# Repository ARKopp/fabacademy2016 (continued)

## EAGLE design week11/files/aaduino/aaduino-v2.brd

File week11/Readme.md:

[BACK to START](../)

[FINAL PROJECT](../final) / [WEEK 1](../week1) / [COMPUTER AIDED DESIGN](../week2) / [COMPUTER-CONTROLLED-CUTTING](../week3) / [ELECTRONICS PRODUCTION](../week4) / [3D SCANNING & PRINTING](../week5) / [ELECTRONICS DESIGN](../week6)  / [COMPUTER-CONTROLLED MACHINING](../week7) / [EMBEDDED PROGRAMING ](../week8) / [MECHANICAL DESIGN](../week9) / [MACHINE DESIGN](../week10) / [INPUT DEVICES](../week11) / [3D MOLDING AND CASTING](../week12) / [OUTPUT DEVICES](../week13) / [COMPOSITES](../week14) / [EMBEDDED NETWORKING & COMMUNICATIONS](../week15) / [INTERFACE AND APPLICATION PROGRAMMING ](../week16) / [APPLICATIONS AND IMPLICATIONS ](../week17) / [INVENTION, INTELLECTUAL PROPERTY, AND BUSINESS MODELS](../week18) / [PROJECT DEVELOPMENT ](../week19)  

# Week 11 - INPUT DEVICES
April 13 - April 20 

[Lecture](http://academy.cba.mit.edu/classes/input_devices/index.html), [Video](http://archive.fabacademy.org/archives/2016/master/videos/04-20/index.html)

~~~
*Weeks Assignment*

* measure something
* add a sensor to a micro controller board that you have designed and read it

~~~

## Hall effect Sensor Board

I was waiting for this assignment as I already wanted to measure the speed of my penny board for some time so I decided to make the Hall effect Sensor Board.

First I looked in the Fab Academy Inventory for the parts number of the Hall Sensor called A1301 from Allegro with the Part Number 620-1021-1-ND and then I looked on the Digikey website for the [datasheet](http://www.digikey.de/product-search/de?keywords=620-1021-1-ND). If you would order it from Digikey Germany a sensor would be 1,77€ when you buy ten the cost would be 1,38€.

### The Hall Effect (part 2 on the [Output](../week13) page)

The Hall Effect describes a voltage difference across an conductor whenever a magnetic field is applied in a direction prependicular to the flow of the current of the conductor.

This means whenever the hall sensor detects a magnet it outputs a High Voltage to its Output pin (VOUT). So by clueing a magnet to the wheel of my pennyboard and putting the Hall Sensor Board next to it I can measure the times I get an Output and then with the radius of my wheel I can calcualte the speed of my board in m/s and km/h.

After reading the datasheet I understood that the Hall Sensor A1301 I got has a maximum Output voltage of 50% of the input Voltage and the Output Voltage proportional to the magnetic field supplied. So I decided to use a neodyne magnet to make sure I get a good output. 

### Bill of Materials

SMD Components for the Hall Sensor:	

* IC2 A1324 (SOT-23) (Hall Sensor)
* FTDI Connector
* 2x3 ISP Connector
* Attiny45
* 10k Resistor
* 1uF Capacitor
* neodyn magnet
* a skaeteboard

I also decided to add 2 LEDs.

* 2 X LED green
* 2 X Resistor 499 Ohm 

Neils design I started with.

### My Schematic

I got all the components together and added them to my schematic. I just  could not find the hall sensor at first in eagle.  Finally I looked in the datasheet and found that the name for the hall sensor is A1324-26 or SOT-23. With SOT-23 I found it at last. I  decided this time to also connect all the components to understand the schematic better. The LEDS I connected to MISO and to MOSI. Also I added GND and VCC to all the components. I had to look in another library for them called Supply1.

### Setting up your libraries correctly

After that problem of not finding the components I did some more research into how I can set up my libraries correctly. I figured out that I have to click on the button "load all libraries". I also installed the adafruit library. [This tutorial](https://learn.sparkfun.com/tutorials/how-to-install-and-setup-eagle/using-the-sparkfun-libraries) on sparkfun helped me out. 
And now I finally see all the libraries wenn I click on add components. 

### Designing the traces

To make things a bit more fun I wanted to make a space invader design of my board. So I first drew a rough design with the eyes on top but I did not manage to connect all the components without using 0Ohm Resistors so I took Neils Design as a guideline and went from there. I also put the leds in the bottom. Then I did a first export and overlaid it with a space invader in gimp. I realized I need much more practice in gimp. I could not use photoshop because I do not have a license anymore. 

After like 15 iteration going back and forth between eagle and gimp making the traces smaller and splitting up the pads I finally got my final space invader hall sensor board Version1 at the end of the day.

To get the design through the Design Rules I had to make the traces smaller. Still I did not manage to go through the hall sensor with the ground but I will fix that later with my knife.  

###  Prepare and Mill

My first try was a fail as I used 8mil in eagle Design Rules instead if 16 mil so the traces where to small. 

So I changed the Design Rules to 16 mil and exported the boad again and did the gimp operation.

### Postprocess, Stuffing and Soldering

***Update 23. April***

Finally in Valldaura on Saturday I finished stuffing and soldering the Invader. 

Before soldering I used my knife to get rid of some thin copper in between the traces. 

I think I got these problems because I made my traces thinner and then I would need to put in fabmodules that I want more the 50% overlap. 

### Connecting the Cables

This time we are using Rx, 5v and GND of the FTDI cable and connect them to the Invader.  

### Flash Attiny with Neils C code

For programing I saved the make, the c and the python file from the academy site in one directory and opened the folder in Terminal.

```
sudo make -f hello.mag.45.make program-usbtiny
```

and it worked. 

### Program Attiny with Neils Python Code

Then I tried to run the python program.

I needed to install brew, python and pyserial

```
brew install python
```

```
python hello.mag.45.py /dev/tty.
```

And then hit TAB to autocomplete your serial port. In my case it was this. 

```
python hello.mag.45.py /dev/tty.SLAB_USBtoUART
```

But I got an error that the serial modul is not installed. So I installed it. 

```
sudo easy_install pyserial
```

Now I am getting an error that the port is not working.

After not getting it to work with my FTDI Cable I used a different Cable and got it to worked. 

***Update 30. April 2016:***

It was not the cable I have just connected the pins wrongly. 

```
python hello.mag.45.py /dev/tty.usbserial
```

Also when I put a magnet close to it it worked. 

To show the output of the sensor I installed [python-tk](https://wiki.python.org/moin/TkInter) before  which is a python Web User Interface.

### Change the code to turn on the LEDs

Ok the next step is to look into the C ode Neil and change it to turn on my LED. I looked at the C Code but I still understand too little C so I decided to switch to the Arduino IDE. 

First I looked at the [Attiny45 Datasheet ](http://www.atmel.com/images/atmel-2586-avr-8-bit-microcontroller-attiny25-attiny45-attiny85_datasheet-summary.pdf) to find out the pin Numbering and then also googled what would be the pins then in Arduino.  

I remember I connected the LEDs to MISO and MOSI which would be Leg6/Pin 1 and Leg5/PIN0.

I opened the Ardunio IDE, chose Platine --> ATtiny x5 series, Chip --> Attin45, Clock --> 8Mhz internal (standard is 1mhZ), Port --> dev/cu.SLAB_USBtoUART and --> Programmer USBtinyISP. 

The upload workded but I do not get the LEDs to turn on. I tried every pin. I think that is a great strategy to find the the right pin. 

So first I checked the the LEDs again. I have soldered them correctly with the Green Line to the Ground. So I check the Value again. I used red Led and after looking into the [Fabacademy Inventory](https://docs.google.com/spreadsheets/d/1U-jcBWOJEjBT5A0N84IUubtcHKMEMtndQPLCkZCkVsU/pub?single=true&gid=0&output=html) I found the Red Led had the number 160-1167-2-ND. Looking that up on the digikey website I found the Forward Voltage is 1.8 V and the forward current is 40 mA which resulted in a Resistor of 82 Ohms and I am using 499 Ohms at the moment so I will change the resistor to 100 Ohms. 

In [Output Devices](../week13) I resolved that issue finally and got the LEDs to light up. 

## Otherduino

I already tried to cut the Otherduino as a second project with my new othermill but I used only a once sided FR2 board and the design was two sided. I only used the mill for two cuts but the otherplan software is great. You can directly use the brd files from Eagle and do not have to prepare traces and outline images in gimp or photoshop.

I will try again when I am home in Munich. There is a great [instructable](http://www.instructables.com/id/Unlimited-Arduino-clones-the-Otherduino/?ALLSTEPS) for it. 

**Update 3. Mai 2015:**

Now I got a 2 sided FR2 and I tried to cut the Arduino again. It cut beatfifully with the Othermill I just had to postprocess a little. The machine is great it tells you when to change tool and you can easily produce two sided PCBs

**The process with the Othermill:** 

Bill of Material (all through hole components)

* Circuit board, double-sided
* Clock crystal, 16MHz
* Resistor, 10K*
* 2x Capacitor, 0.1uF
* 2x Capacitors, 22pf
* LED, amber and green or pick your two favorite colors*
* Resistors, 220 ohm (2)*
* Male header, 6-pin, right angle
* Female headers, 20-pin, straight (2)
* ATmega328 microcontroller with Arduino bootloader 
* Chip socket, 28-pin

I did not buy any of the components but looked around at my used electronics and found all the parts. 

First I soldered the Vias which are the connections between the bottom and the top. 

The Otherduino next to my first [Arduino Duemilanove from 2009](https://www.arduino.cc/en/Main/arduinoBoardDuemilanove) which I took the ATmega328 chip and the 16 mhz clock from. 

Then I soldered the chip and the other components. At first I soldered the chip wrongly so I had to desolder it and resolder it.

I checked everything put I could not upload a sketch yet. 

***Update 23. Mail 2016***

I checked all connections and was able to upload a sketch but could not get the light to blink.

I will try to get anothter light to blink tomorrow.

Optional external power materials:

* DC barrel jack, 2.1mm if you want to connect to a wall-wart style power supply
* Regulator, 5V if you want to regulate the wall jack or other power supply to 5V; some are already 5V
* Regulator, 3.3V if you want the option of 3.3 volts. If you want a barrel jack, the 5V regulator is also required.
* Capacitor, 10uF* for each regulator; you'll need two if you're using both regulators

## AAduino

In this week I saw an article on techcrunch of an Arduino in a AA Battery case.

I am also getting together all the components to make [this arduino](https://github.com/kanflo/aaduino) as well. 

* 1/100 flat and mill (
* [x] double sided PCB
* [x] ATMega328p --> [digikey](http://www.digikey.com/product-detail/en/atmel/ATMEGA328P-AUR/ATMEGA328P-AURTR-ND/2357086))
* [ ] temp sensor DS18B20 -> [digikey](http://www.digikey.com/product-detail/en/maxim-integrated/DS18B20/DS18B20-ND/420071)
* [x] 1 x 0603 10K resistor
* [ ] 5 x 0603 0.1uF ceramic capacitors
* [ ] 1 x 0603 1uF ceramic capacitor
* [x] 0603 10uF ceramic capacitor
* [ ] SMT ceramic resonator 16.0MHz
* [x] 2x3 Header
* [x] 3x1 Header
* [ ]  RFM69C Sub-GHz transceiver module

***Update 19. Mai 2016:***

After doing almost all output device boards I got a better understanding of Eagle. I think taking a design of somebody else and look for the components and then change it is a great way to get even a step further. 

[Here](https://nathan.chantrell.net/20130923/tiny328-mini-wireless-arduino-clone/) are all the files and a good explanation. 

## Other Input Devices I want to do later

### Switch

* Attiny45
* Switch
* 2x3 Connector
* FTDI Connector
* 10k 
* 1uF

### Motion

* Attiny45
* FTDI
* 2x3 ISP
* 10k
* 1uF
* HC-Sr04

### Distance

* HC-SR501
* Attiny45
* 1uF
* 10k
* FTDI
* 2x3 ISP

### Temperature

* 4x10k
* 1uF
* FTDI
* Attiny45

### Light

* 49.9k
* Attiny45
* 10k
* T1
* 1uF

### Acceleration 

* ADXL343
* 3 x 10K
* 3V Regulator
* 2x3 ISP Connector
* 1uF
* FTDI

### Sound

* FTDI 
* Attiny45
* 2x3 ISP
* 4 x 10k
* O Ohm
* 3x  1 uF

### Step Response

#

* 2x2 ISP
* 2x3 ISP
* Attiny 45
* 10K
* 1uF
* 1M
* FTDI

## Project Files

[Download](https://drive.google.com/folderview?id=0B3iYmii-HJ7TaWk0RDZWTGktM00&usp=sharing) all project files from this assignment from my Google Drive or directly from here. 

[hall_sensor.brd](./files/hall_sensor/hall_sensor.brd)

[hall_sensor.sch](./files/hall_sensor/hall_sensor.sch)

[hall_sensor_outline.png](./files/hall_sensor/hall_sensor_outline.png)

[hall_sensor_traces.png](./files/hall_sensor/hall_sensor_traces.png)

[hello.mag.45.make](./files/hall_sensor/hello.mag.45.make)

[hello.mag.45.c](./files/hall_sensor/hello.mag.45.c)

[hello.mag.45.py](./files/hall_sensor/hello.mag.45.py)

[blink_input.ino](./files/blink_input/blink_input.ino)

[Otherduino.brd](./files/otherduino/Otherduino5r.brd)

## Learnings

 * Deeper knowledge in Gimp now
 * Code in C
 * Calculate LED Resistors
 * Solder Vias
 * Mill a two sided board
 * Troubleshot a PCBr

## Feedback

[Twitter](http://www.twitter.com/andreaskopp) me or [email me at andreasrkopp at gmail dot com](mailto:andreasrkopp@gmail.com).

[BACK to TOP](../week11)

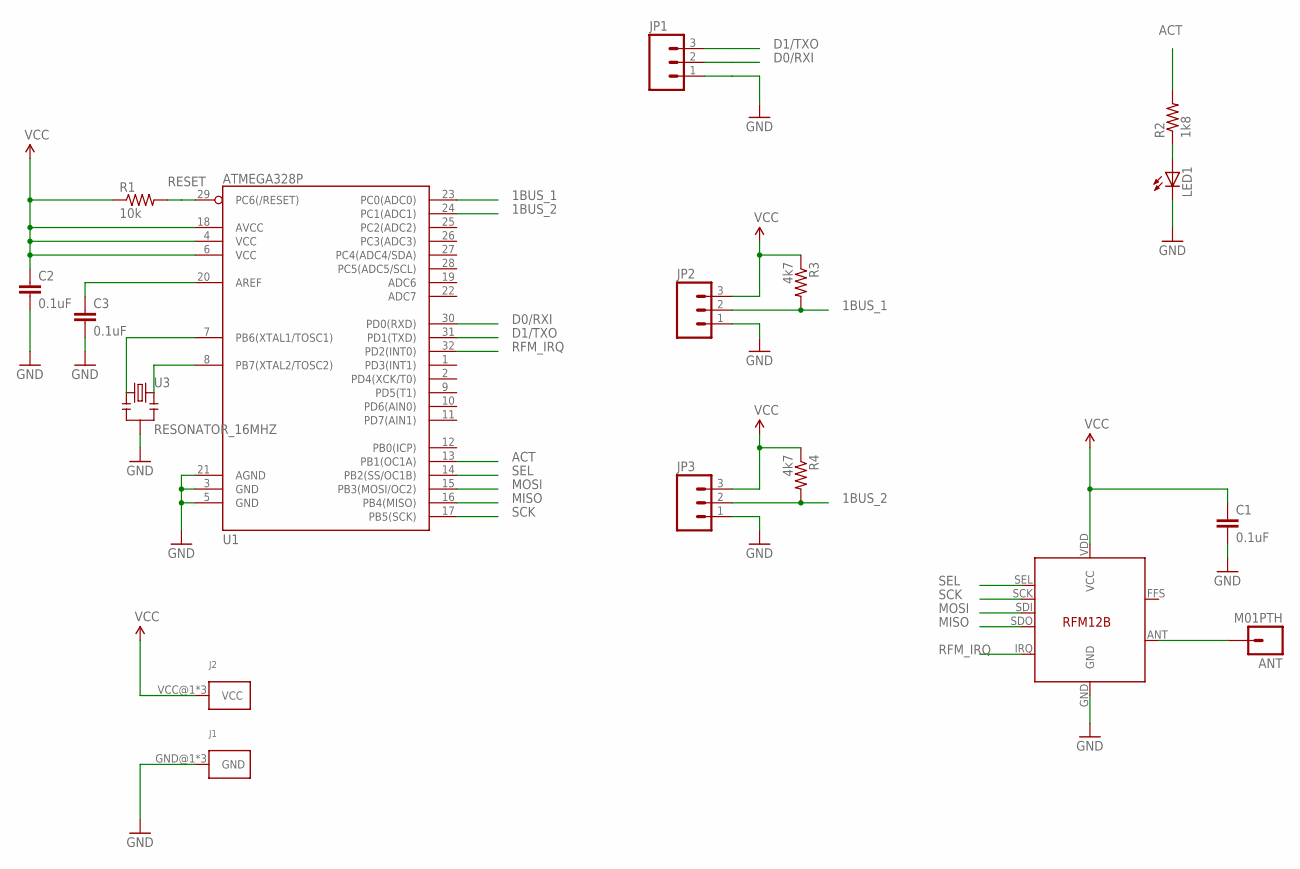
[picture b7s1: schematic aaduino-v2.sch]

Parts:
ANT: M01PTH; 1X01
C1, C2, C3: 0.1uF; 0603-CAP
J1: KEYSTONE-629; KEYSTONE_AA_AAA_BATTERY_TERMINAL-629
J2: KEYSTONE-637; KEYSTONE_AA_AAA_BATTERY_TERMINAL-637
JP1, JP2, JP3: M03PTH; 1X03
LED1: LED0603; LED-0603
R1: 10k; 0603-RES
R2: 1k8; 0603-RES
R3, R4: 4k7; 0603-RES
U1: ATMEGA328P; TQFP32-08
U2: RFM12B
U3: RESONATOR_16MHZ; RESONATOR_SMD

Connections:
1BUS_1: JP2.2, R3.2, U1.23 (PC0(ADC0))
1BUS_2: JP3.2, R4.2, U1.24 (PC1(ADC1))
ACT: R2.2, U1.13 (PB1(OC1A))
D0/RXI: JP1.2, U1.30 (PD0(RXD))
D1/TXO: JP1.3, U1.31 (PD1(TXD))
GND: C1.2, C2.2, C3.2, J1.GND@1, J1.GND@2, J1.GND@3, JP1.1, JP2.1, JP3.1, LED1.C, U1.3 (GND), U1.5 (GND), U1.21 (AGND), U2.GND, U3.2
MISO: U1.16 (PB4(MISO)), U2.SDO
MOSI: U1.15 (PB3(MOSI/OC2)), U2.SDI
unnamed: LED1.A, R2.1
unnamed: C3.1, U1.20 (AREF)
unnamed: U1.7 (PB6(XTAL1/TOSC1)), U3.1
unnamed: U1.8 (PB7(XTAL2/TOSC2)), U3.3
unnamed: ANT.1, U2.ANT
RESET: R1.2, U1.29 (PC6(/RESET))
RFM_IRQ: U1.32 (PD2(INT0)), U2.IRQ
SCK: U1.17 (PB5(SCK)), U2.SCK
SEL: U1.14 (PB2(SS/OC1B)), U2.SEL
VCC: C1.1, C2.1, J2.VCC@1, J2.VCC@2, J2.VCC@3, JP2.3, JP3.3, R1.1, R3.1, R4.1, U1.4 (VCC), U1.6 (VCC), U1.18 (AVCC), U2.VDD (VCC)

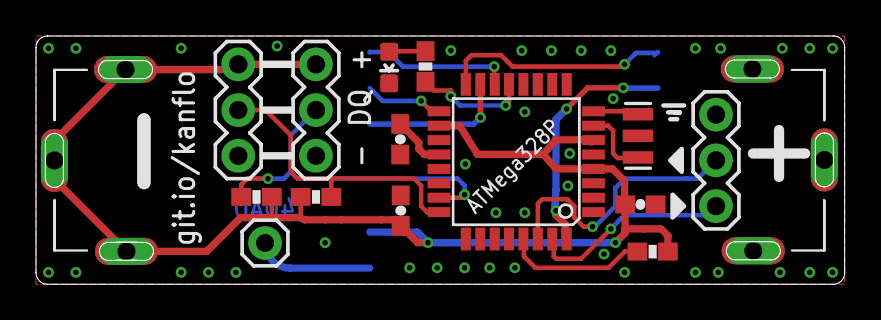
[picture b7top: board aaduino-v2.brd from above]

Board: 2 copper layers, 44.9 x 13.8 mm, 17 parts (1 on the bottom side), 18 nets.

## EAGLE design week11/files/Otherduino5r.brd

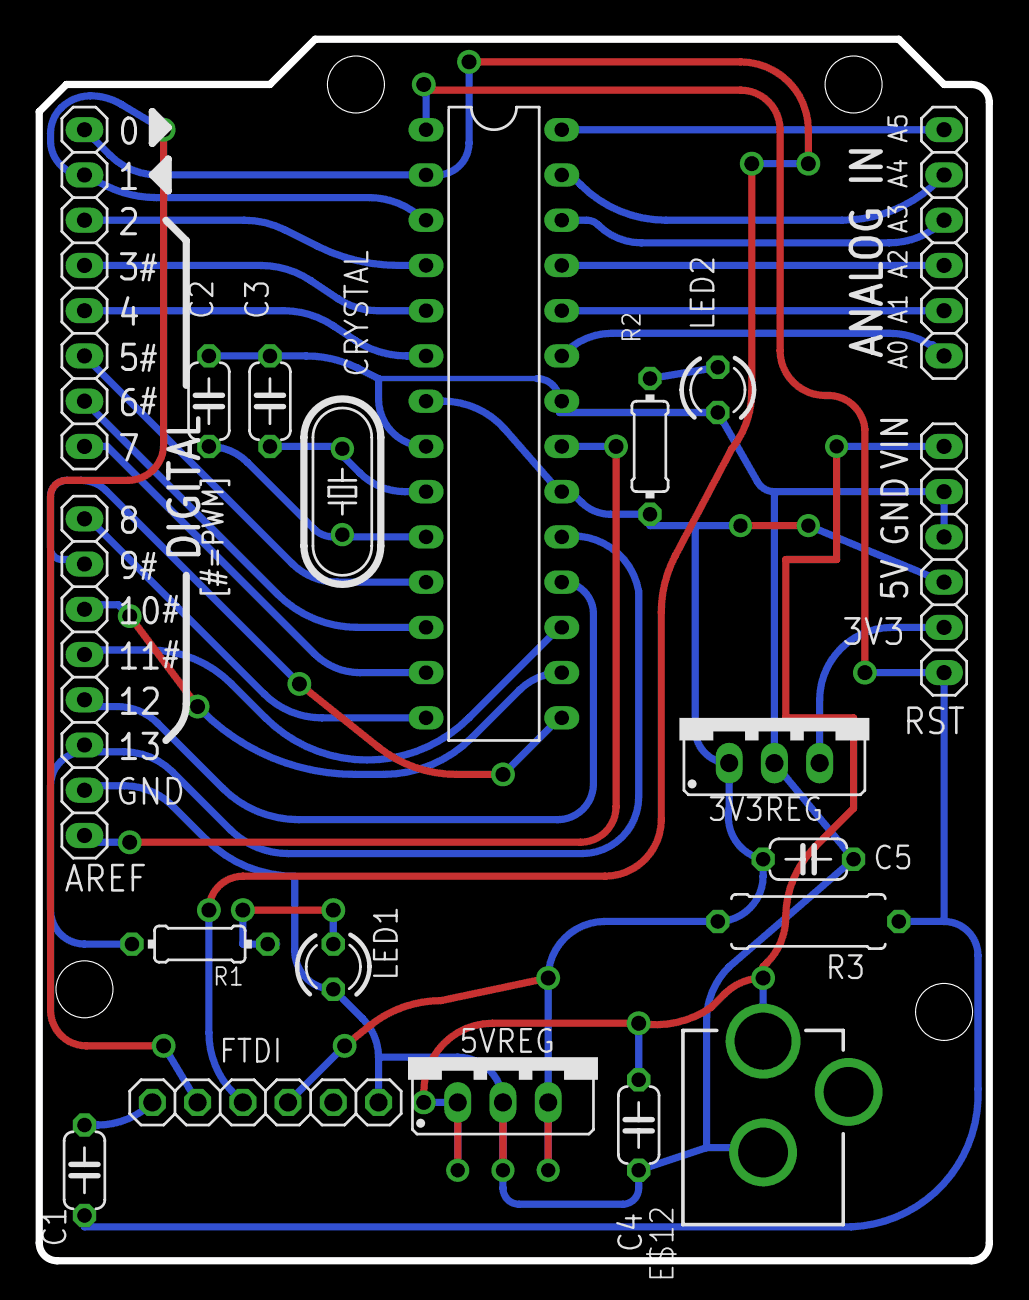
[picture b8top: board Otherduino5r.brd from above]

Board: 2 copper layers, 53.3 x 68.6 mm, 20 parts (0 on the bottom side), 31 nets.

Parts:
3V3REG, 5VREG: 78XXS
AD, AD1: 6x1F-H8.5; 1X06
C1: 0.1uF; C050-024X044
C2, C3: 22pF; C050-024X044
C4, C5: 10uF; C050-024X044
CRYSTAL: 16MHz; HC49/S
E$12: DCJACK_2MM_PTH
FTDI: 1X06
IOL, IOL1: 8x1F-H8.5; 1X08
LED1, LED2: LED3MM
R1, R2: 220; 0204/7
R3: 10k; 0309/10
ZU4: ATMEGA328P-PU; DIL28-3

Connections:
S$1: LED1.A, R1.1
S$2: IOL.3, ZU4.4
S$4: FTDI.5, IOL.2, ZU4.3
S$5: IOL.4, ZU4.5
S$6: IOL.5, ZU4.6
S$9: C3.1, CRYSTAL.1, ZU4.9
S$10: 3V3REG.OUT, AD1.2
S$11: 5VREG.IN, AD1.6, C4.1, E$12.PWR
S$14: C2.1, CRYSTAL.2, ZU4.10
S$16: IOL.7, ZU4.12
S$17: IOL.8, ZU4.13
S$18: IOL1.1, ZU4.14
S$19: IOL1.2, ZU4.15
S$20: IOL1.3, ZU4.16
S$21: IOL1.4, ZU4.17
S$22: IOL1.5, ZU4.18
S$23: IOL1.6, R1.2, ZU4.19
S$24: AD.1, ZU4.23
S$25: AD.2, ZU4.24
S$26: AD.3, ZU4.25
S$27: 3V3REG.GND, 5VREG.GND, AD1.4, AD1.5, C2.2, C3.2, C4.2, C5.2, E$12.GND, FTDI.1, IOL1.7, LED1.K, LED2.K, ZU4.8
S$28: AD.4, ZU4.26
S$29: AD.5, ZU4.27
S$30: AD.6, ZU4.28
S$31: IOL.6, ZU4.11
S$32: C1.2, FTDI.6
S$33: 3V3REG.IN, 5VREG.OUT, AD1.3, C5.1, FTDI.3, R2.2, R3.1, ZU4.7, ZU4.20
S$34: IOL1.8, ZU4.21
S$38: LED2.A, R2.1
S$40: AD1.1, C1.1, R3.2, ZU4.1
S$42: FTDI.4, IOL.1, ZU4.2

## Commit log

2016-02-05 hallo
2016-02-08 arbeite an erster Woche
2016-02-08 work in progess
2016-02-09 navigation added
2016-02-09 sites updated
2016-02-10 updatet week1
2016-02-10 title updated
2016-02-10 week 1 updatet
2016-02-15 pdf deleted
2016-04-06 week 9
2016-05-31 update big
2016-05-31 Add Gitter badge
2016-05-31 added gitter
2016-05-31 chatter badges
2016-06-04 update week 18
2016-06-05 big update
2016-06-13 firmware update
2016-06-20 update final project June19
2016-07-05 update last week
